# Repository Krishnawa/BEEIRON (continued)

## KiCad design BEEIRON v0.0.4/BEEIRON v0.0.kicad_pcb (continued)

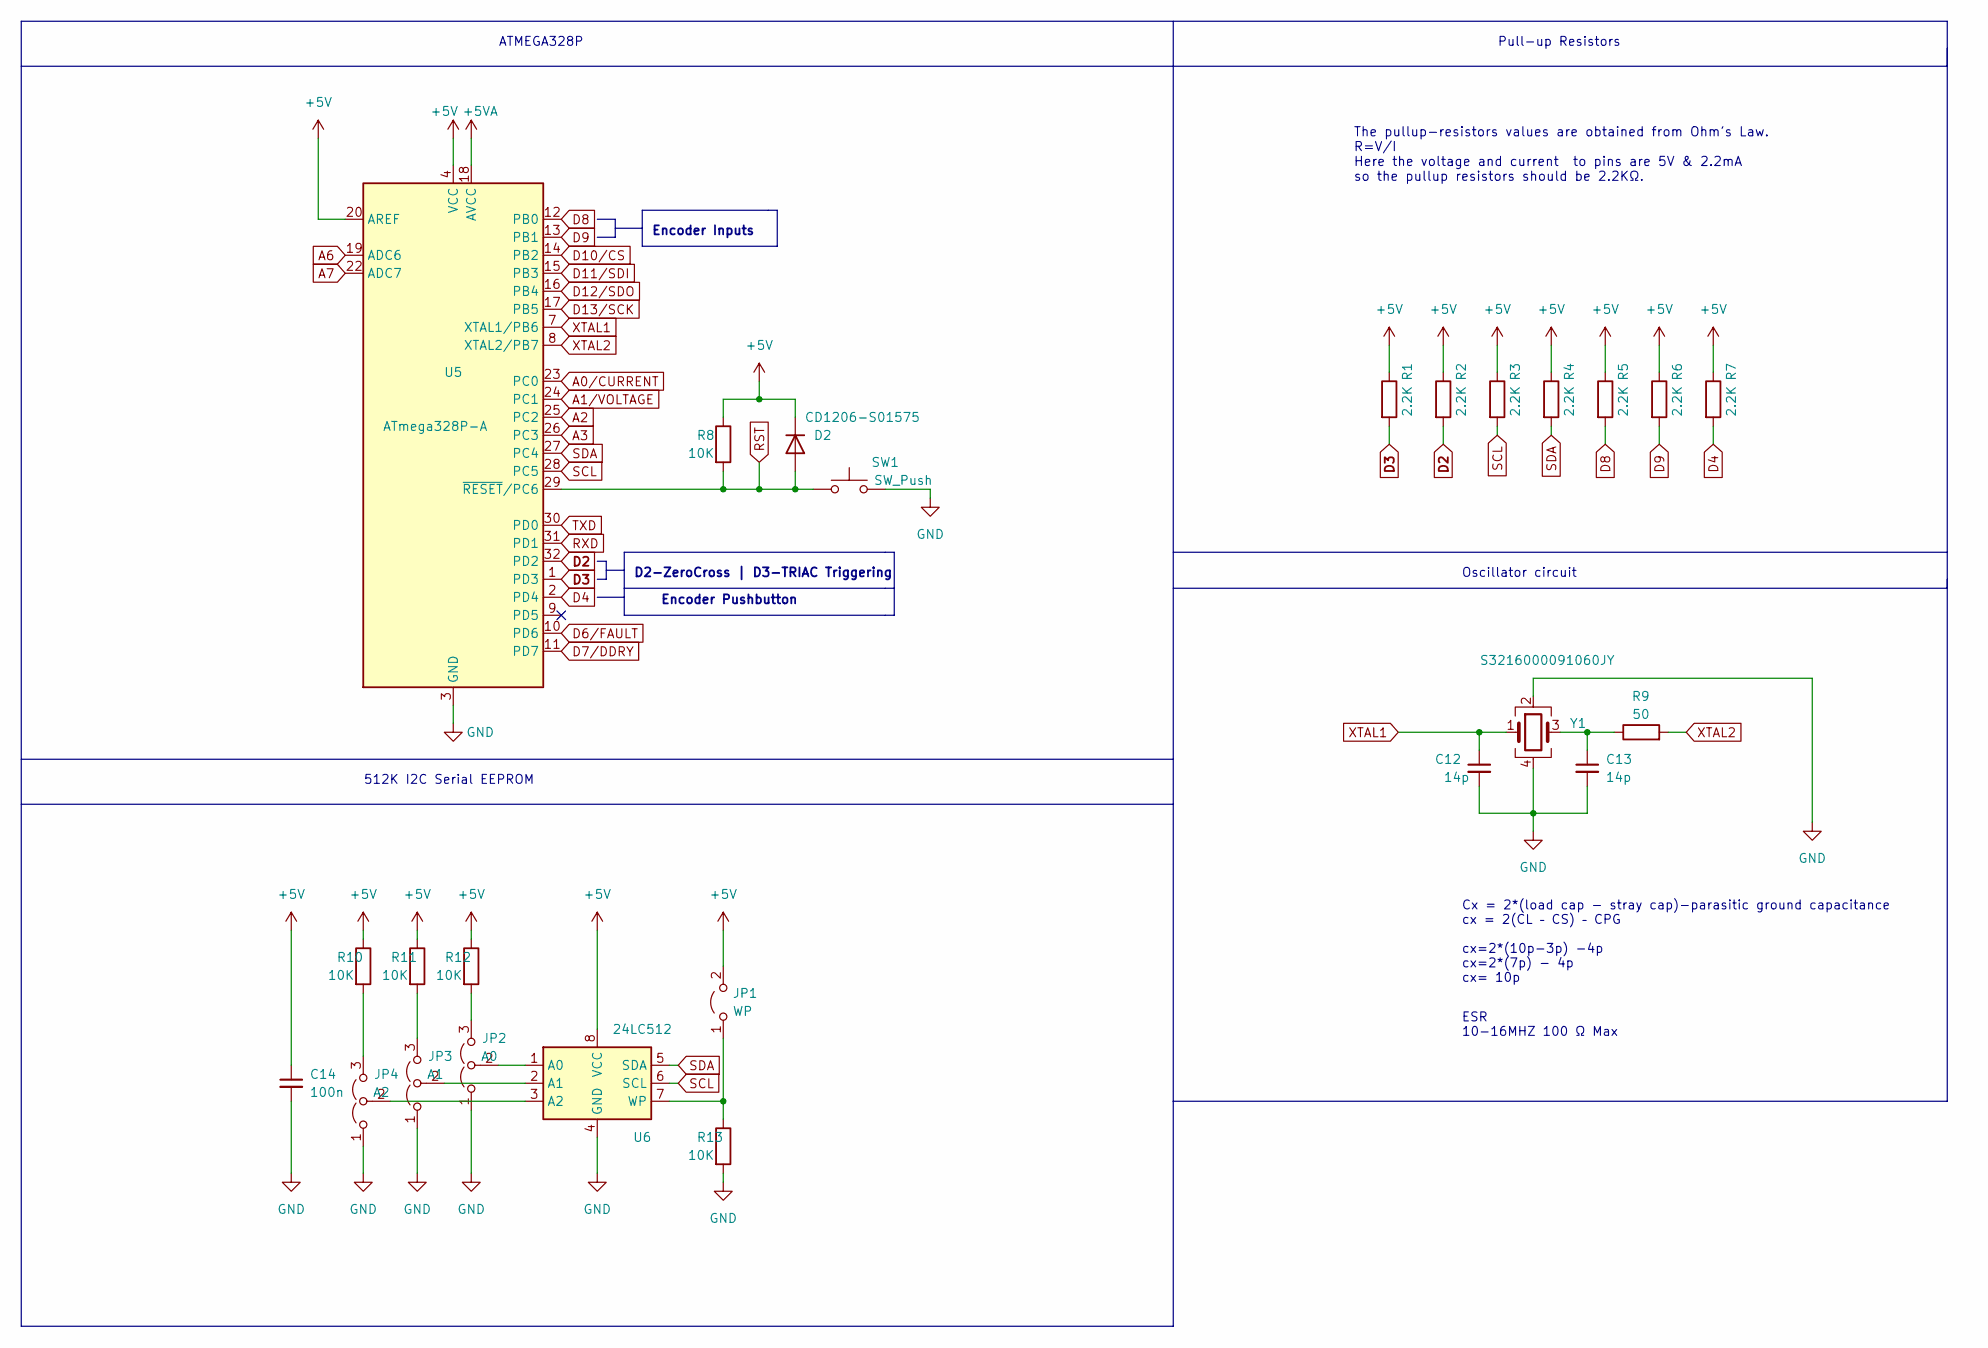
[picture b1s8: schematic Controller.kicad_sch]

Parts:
C12, C13: 14p; C_0805_2012Metric
C14: 100n; C_0805_2012Metric
D2: CD1206-S01575; D_1206_3216Metric
JP1: WP; SolderJumper-2_P1.3mm_Open_TrianglePad1.0x1.5mm
JP2: A0; SolderJumper-3_P2.0mm_Open_TrianglePad1.0x1.5mm
JP3: A1; SolderJumper-3_P2.0mm_Open_TrianglePad1.0x1.5mm
JP4: A2; SolderJumper-3_P2.0mm_Open_TrianglePad1.0x1.5mm
R1, R2, R3, R4, R5, R6, R7: 2.2K; R_0805_2012Metric
R8, R10, R11, R12, R13: 10K; R_0805_2012Metric
R9: 50; R_0805_2012Metric
SW1: SW_Push; SW_SPST_CK_RS282G05A3
U5: ATmega328P-A; TQFP-32_7x7mm_P0.8mm
U6: 24LC512; SOIC-8_3.9x4.9mm_P1.27mm
Y1: S3216000091060JY; Crystal_SMD_3225-4Pin_3.2x2.5mm_HandSoldering

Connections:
+5V: C14.1, D2.1 (K), JP1.2 (B), R1.1, R2.1, R3.1, R4.1, R5.1, R6.1, R7.1, R8.1, R10.1, R11.1, R12.1, U5.4 (VCC), U5.6 (VCC), U5.20 (AREF), U6.8 (VCC); also elsewhere on the board
+5VA: U5.18 (AVCC); also elsewhere on the board
A0/CURRENT: U5.23 (PC0); also elsewhere on the board
A1/VOLTAGE: U5.24 (PC1); also elsewhere on the board
A2: U5.25 (PC2); also elsewhere on the board
A3: U5.26 (PC3); also elsewhere on the board
A6: U5.19 (ADC6); also elsewhere on the board
A7: U5.22 (ADC7); also elsewhere on the board
D2: R2.2, U5.32 (PD2); also elsewhere on the board
D3: R1.2, U5.1 (PD3); also elsewhere on the board
D4: R7.2, U5.2 (PD4); also elsewhere on the board
D6/FAULT: U5.10 (PD6); also elsewhere on the board
D7/DDRY: U5.11 (PD7); also elsewhere on the board
D8: R5.2, U5.12 (PB0); also elsewhere on the board
D9: R6.2, U5.13 (PB1); also elsewhere on the board
D10/CS: U5.14 (PB2); also elsewhere on the board
D11/SDI: U5.15 (PB3); also elsewhere on the board
D12/SDO: U5.16 (PB4); also elsewhere on the board
D13/SCK: U5.17 (PB5); also elsewhere on the board
GND: C12.2, C13.2, C14.2, JP2.1 (A), JP3.1 (A), JP4.1 (A), R13.2, SW1.2, U5.3 (GND), U5.5 (GND), U5.21 (GND), U6.4 (GND), Y1.2, Y1.4; also elsewhere on the board
unnamed: C13.1, R9.1, Y1.3
unnamed: JP1.1 (A), R13.1, U6.7 (WP)
unnamed: JP2.2 (C), U6.1 (A0)
unnamed: JP2.3 (B), R12.2
unnamed: JP3.2 (C), U6.2 (A1)
unnamed: JP3.3 (B), R11.2
unnamed: JP4.2 (C), U6.3 (A2)
unnamed: JP4.3 (B), R10.2
RST: D2.2 (A), R8.2, SW1.1, U5.29 (~RESET/PC6); also elsewhere on the board
RXD: U5.31 (PD1); also elsewhere on the board
SCL: R3.2, U5.28 (PC5), U6.6 (SCL); also elsewhere on the board
SDA: R4.2, U5.27 (PC4), U6.5 (SDA); also elsewhere on the board
TXD: U5.30 (PD0); also elsewhere on the board
XTAL1: C12.1, U5.7 (XTAL1/PB6), Y1.1
XTAL2: R9.2, U5.8 (XTAL2/PB7)

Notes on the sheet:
Cx = 2*(load cap - stray cap)-parasitic ground capacitance cx = 2(CL – CS) – CPG cx=2*(10p-3p) -4p cx=2*(7p) - 4p cx= 10p
The pullup-resistors values are obtained from Ohm's Law. R=V/I Here the voltage and current to pins are 5V & 2.2mA so the pullup resistors should be 2.2KΩ.
Encoder Inputs
ESR 10-16MHZ 100 Ω Max
D2-ZeroCross | D3-TRIAC Triggering
ATMEGA328P
Oscillator circuit
Encoder Pushbutton
Pull-up Resistors
512K I2C Serial EEPROM

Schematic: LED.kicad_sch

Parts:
DL1: L; LED_0603_1608Metric
DON1: ON; LED_0603_1608Metric
R36, R37, R38, R39: 10K; R_0805_2012Metric
RXD1: RXD; LED_0603_1608Metric
TXD1: TXD; LED_0603_1608Metric

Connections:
+5V: R36.1, R37.1, R39.1; also elsewhere on the board
D13/SCK: R38.1; also elsewhere on the board
GND: DL1.1 (K), DON1.1 (K); also elsewhere on the board
unnamed: DL1.2 (A), R38.2
unnamed: DON1.2 (A), R39.2
unnamed: R36.2, RXD1.2 (A)
unnamed: R37.2, TXD1.2 (A)
RXD: RXD1.1 (K); also elsewhere on the board
TXD: TXD1.1 (K); also elsewhere on the board

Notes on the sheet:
LED Indicators

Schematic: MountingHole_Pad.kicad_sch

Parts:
H1, H2, H3, H4: MountingHole_Pad; MountingHole_5mm_Pad_Via

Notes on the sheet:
Mounting Holes

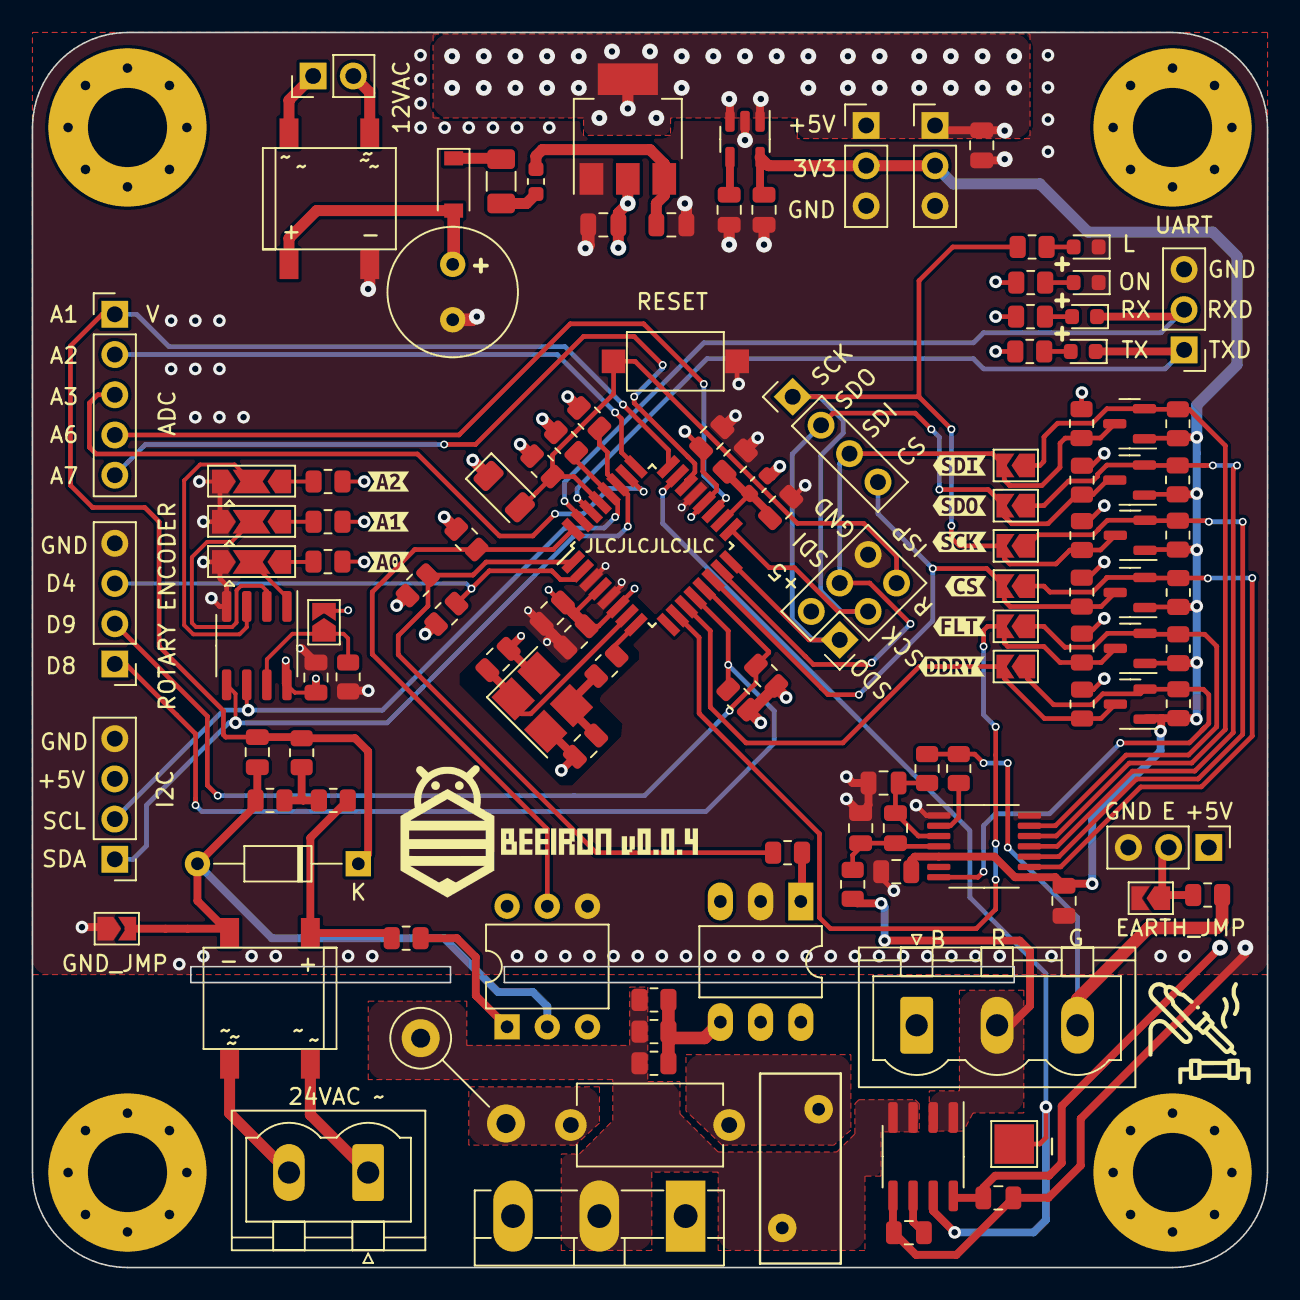
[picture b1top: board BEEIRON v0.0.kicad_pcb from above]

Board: 4 copper layers, 78.0 x 78.0 mm, 133 parts (0 on the bottom side), 71 nets.

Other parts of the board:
kibuzzard-619F1F8F: G***; kibuzzard-619F1F8F
kibuzzard-619F1F9A: G***; kibuzzard-619F1F9A
kibuzzard-619F1F60: G***; kibuzzard-619F1F60
kibuzzard-6198C8A0: G***; kibuzzard-6198C8A0
kibuzzard-6198C8AE: G***; kibuzzard-6198C8AE
kibuzzard-6198C8D5: G***; kibuzzard-6198C8D5
kibuzzard-6198C8F1: G***; kibuzzard-6198C8F1
kibuzzard-6198C887: G***; kibuzzard-6198C887
kibuzzard-6198C929: G***; kibuzzard-6198C929

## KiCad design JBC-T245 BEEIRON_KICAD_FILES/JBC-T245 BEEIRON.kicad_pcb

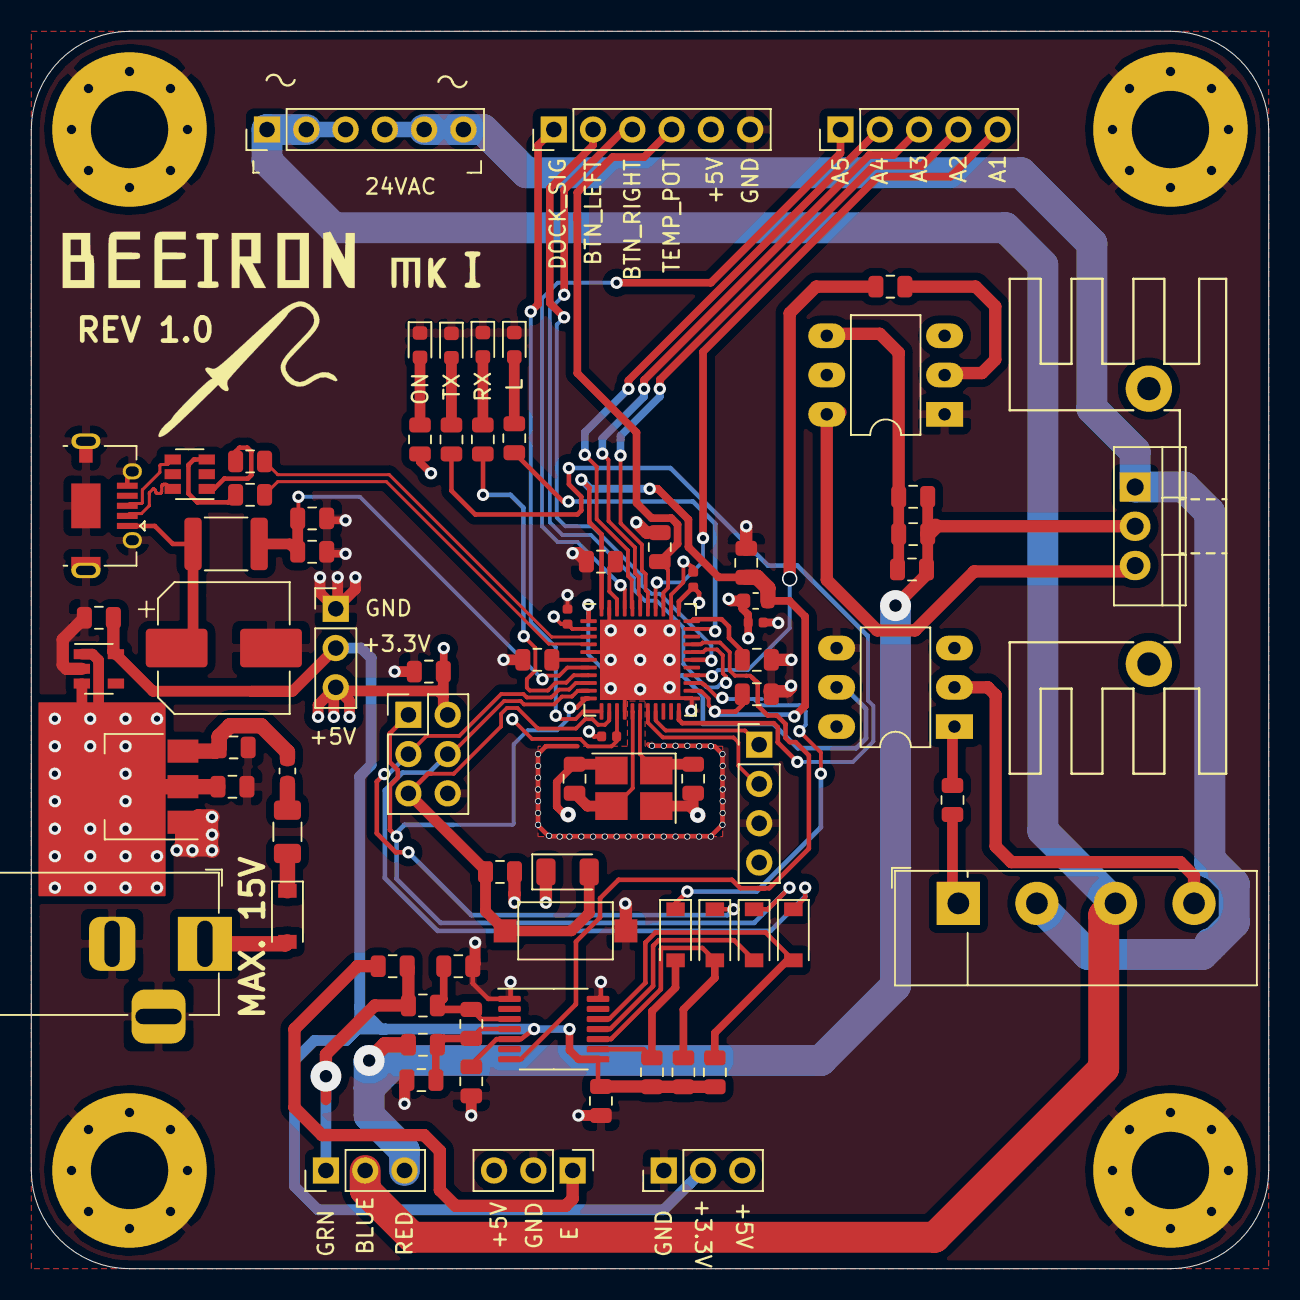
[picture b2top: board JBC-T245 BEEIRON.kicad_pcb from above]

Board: 4 copper layers, 80.0 x 80.0 mm, 83 parts (0 on the bottom side), 64 nets.

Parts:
C1: 10u; CP_Elec_8x5.4
C2, C8, C9, C13, C14, C21: 1u; C_0805_2012Metric
C3: 10n; C_0805_2012Metric
C4, C5, C6, C7: 100n; C_0402_1005Metric
C10, C20, C22: 100n; C_0805_2012Metric
C11, C12: 10u; C_0805_2012Metric
C15, C18, C19: 10nF; C_0805_2012Metric
C16, C17: 40p; C_0805_2012Metric
D1: B5819W; D_SOD-123
D2: CD1206-S01575; D_1206_3216Metric
D3: 4 x 1N4148W; D_SOD-123
D4, D5, D6: 1N4148W; D_SOD-123
D7: KBU1010; Diode_Bridge_Vishay_KBU
F1: 500mA; Fuse_1206_3216Metric
F2: MF-MSMF050-2; Fuse_1812_4532Metric
FB1: FBMH1608HM600-T; L_0603_1608Metric
FB2: 100 @ 100Mhz; L_0603_1608Metric
H1, H2, H3, H4: MountingHole_Pad; MountingHole_5mm_Pad_Via
HS1: Heatsink_Pad_2Pin; Heatsink_Stonecold_HS-132_32x14mm_2xFixation1.5mm
J1, J2, J9, J10: Conn_01x03_Male; PinHeader_1x03_P2.54mm_Vertical
J3: Conn_02x03_Odd_Even; PinHeader_2x03_P2.54mm_Vertical
J4: Conn_01x04_Male; PinHeader_1x04_P2.54mm_Vertical
J5, J11: Conn_01x06_Male; PinHeader_1x06_P2.54mm_Vertical
J6: Conn_01x05_Male; PinHeader_1x05_P2.54mm_Vertical
J7: USB_B_Micro; USB_Micro-AB_Molex_47590-0001
J8: Barrel_Jack_Switch; BarrelJack_Horizontal
L: L; LED_0603_1608Metric
ON: ON; LED_0603_1608Metric
Q1: BT136-500; TO-220-3_Vertical
R1, R2, R4, R5, R18: 10K; R_0805_2012Metric
R3: 3 x 10K; R_0805_2012Metric
R6, R7, R10, R12: 100; R_0805_2012Metric
R8: 10M; R_0805_2012Metric
R9: 3 X100; R_0805_2012Metric
R11: 220; R_0805_2012Metric
R13, R14, R15, R16, R17: 1K; R_0805_2012Metric
R19, R20: 22E; R_0805_2012Metric
RX: RX; LED_0603_1608Metric
SW1: SW_Push; SW_SPST_CK_RS282G05A3
TX: TX; LED_0603_1608Metric
U1: LP2985-3.3; SOT-23-5
U2: NCP1117-5.0_SOT223; SOT-223-3_TabPin2
U3: MAX31856; TSSOP-14_4.4x5mm_P0.65mm
U4: ATmega32U4-MU; QFN-44-1EP_7x7mm_P0.5mm_EP5.2x5.2mm
U5: MOC3020M; DIP-6_W7.62mm_LongPads
U6: USBLC6-2SC6; SOT-23-6
U7: 4N25; DIP-6_W7.62mm_LongPads
Y1: XTY0292-7048; Crystal_SMD_3225-4Pin_3.2x2.5mm_HandSoldering

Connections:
+3V3: C9.1, C13.1, C14.1, J9.2, J10.2, R3.1, R4.1, R5.1, U1.5, U3.5, U3.8
+5V: C4.1, C5.1, C6.1, C7.1, C8.1, C12.1, D2.1, FB1.2, J1.3, J3.2, J4.4, J5.5, J9.3, J10.3, R2.1, R16.1, U1.1, U1.3, U2.2, U4.2, U4.14, U4.34
+5VA: C2.1, C3.1, FB1.1, U4.24, U4.44
A1: J6.5, U4.37
A2: J6.4, U4.38
A3: J6.3, U4.39
A4: J6.2, U4.40
A5: J6.1, U4.41
BTN_LEFT: J5.2, U4.28
BTN_RIGHT: J5.3, U4.29
CS: D3.1, U4.25
D+: J7.3, U6.4
D-: J7.2, U6.6
DOCK_SIG: J5.1, U4.12
DRDY: U3.7, U4.30
Earth_Protective: J1.1, R8.1
GND: C1.2, C2.2, C3.2, C4.2, C5.2, C6.2, C7.2, C8.2, C9.2, C10.2, C11.2, C12.2, C13.2, C14.2, C15.1, C16.2, C17.2, C19.2, C20.2, C21.2, C22.2, H1.1, H2.1, H3.1, H4.1, J1.2, J3.6, J4.3, J5.6, J7.5, J7.6, J8.2, J8.3, J9.1, J10.1, L.1, ON.1, R1.2, R17.2, RX.1, SW1.1, TX.1, U1.2, U2.1, U3.1, U3.14, U4.5, U4.15, U4.23, U4.35, U4.43, U4.45, U5.1, U7.4, Y1.2, Y1.4
HWB: R17.1, U4.33
IRON_BLU: D7.3, J2.2, J11.1, J11.2, J11.3
IRON_GRN: J2.1, R7.2, R8.2
IRON_RED: J2.3, Q1.2, R6.2, R9.2, R10.2, R12.2
LED: R13.1, U4.32
MISO: D5.1, J3.1, U4.11
MOSI: D6.1, J3.4, U4.10
unnamed: C11.1, FB2.1, U2.3
unnamed: C15.2, C18.1, R6.1, U3.4
unnamed: C18.2, C19.1, R7.1, U3.3
unnamed: C20.1, U4.42
unnamed: C21.1, U4.6
unnamed: D1.1, F1.2
unnamed: D3.2, R3.2, U3.9
unnamed: D4.2, R4.2, U3.10
unnamed: D5.2, U3.11
unnamed: D6.2, R5.2, U3.12
unnamed: D7.1, R18.1
unnamed: D7.2, J11.4, J11.5, J11.6, Q1.1
unnamed: D7.4, U7.2
unnamed: L.2, R13.2
unnamed: R14.2, RX.2
unnamed: R15.2, TX.2
unnamed: ON.2, R16.2
unnamed: F1.1, FB2.2
unnamed: Q1.3, U5.6
unnamed: R9.1, R10.1, R12.1, U5.4
unnamed: R11.1, U5.2
unnamed: R18.2, U7.1
unnamed: R19.1, U6.1
unnamed: R20.1, U6.3
PD6: R11.2, U4.26
RD+: R20.2, U4.4
RD-: R19.2, U4.3
RST: D2.2, J3.5, R2.2, SW1.2, U4.13
RX_LED: R14.1, U4.8
SCK: D4.1, J3.3, U4.9
SCL: J4.2, U4.18
SDA: J4.1, U4.19
TEMP_POT: C22.1, J5.4, U4.36
TX_LED: R15.1, U4.22
VBUS: C10.1, F2.1, R1.1, U4.7
VCC: D1.2, J8.1
VUSB1: C1.1, F2.2, J7.1
XTAL1: C16.1, U4.17, Y1.1
XTAL2: C17.1, U4.16, Y1.3
ZERO_CROSS: U4.1, U7.5

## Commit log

2020-09-08 added a image
2021-10-23 version 0.0.3
2021-10-23 remove version 0.0.1 kicad_prl file
2021-10-23 added .gitignore file and Gerber files
2021-10-23 add README_IMG folder and removed backup folders
2021-10-23 move README_IMG to main Folder
2021-10-23 preview the board's top image
2021-10-23 add backup folder
2021-10-24 backup
2021-10-24 added PDF Schematics
2021-10-24 minor edit in the schematics
2021-11-04 Added ibom.html
2021-11-04 Create Preview
2021-11-04 Addes the BOM link
2021-11-11 edit README file
2021-11-21 added bakup file
2021-11-21 Readme changed
2021-11-21 Removed the previous Logic Level Converter and added new Bi-Directional Logic Level Converter for MAX31856
2021-11-23 added 512K I2C Serial EEPROM support
2021-11-23 Removed the backup folder (BEEIRON v0.03-backups)
2021-11-23 added bacup folder in .gitignore
2021-11-25 v0.0.4
2021-11-25 added new image in the README file
